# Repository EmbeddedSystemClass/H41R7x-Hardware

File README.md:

# H41R7x-Hardware
Hexabitz STM32F7/H7 LQFP100 Module Hardware Design

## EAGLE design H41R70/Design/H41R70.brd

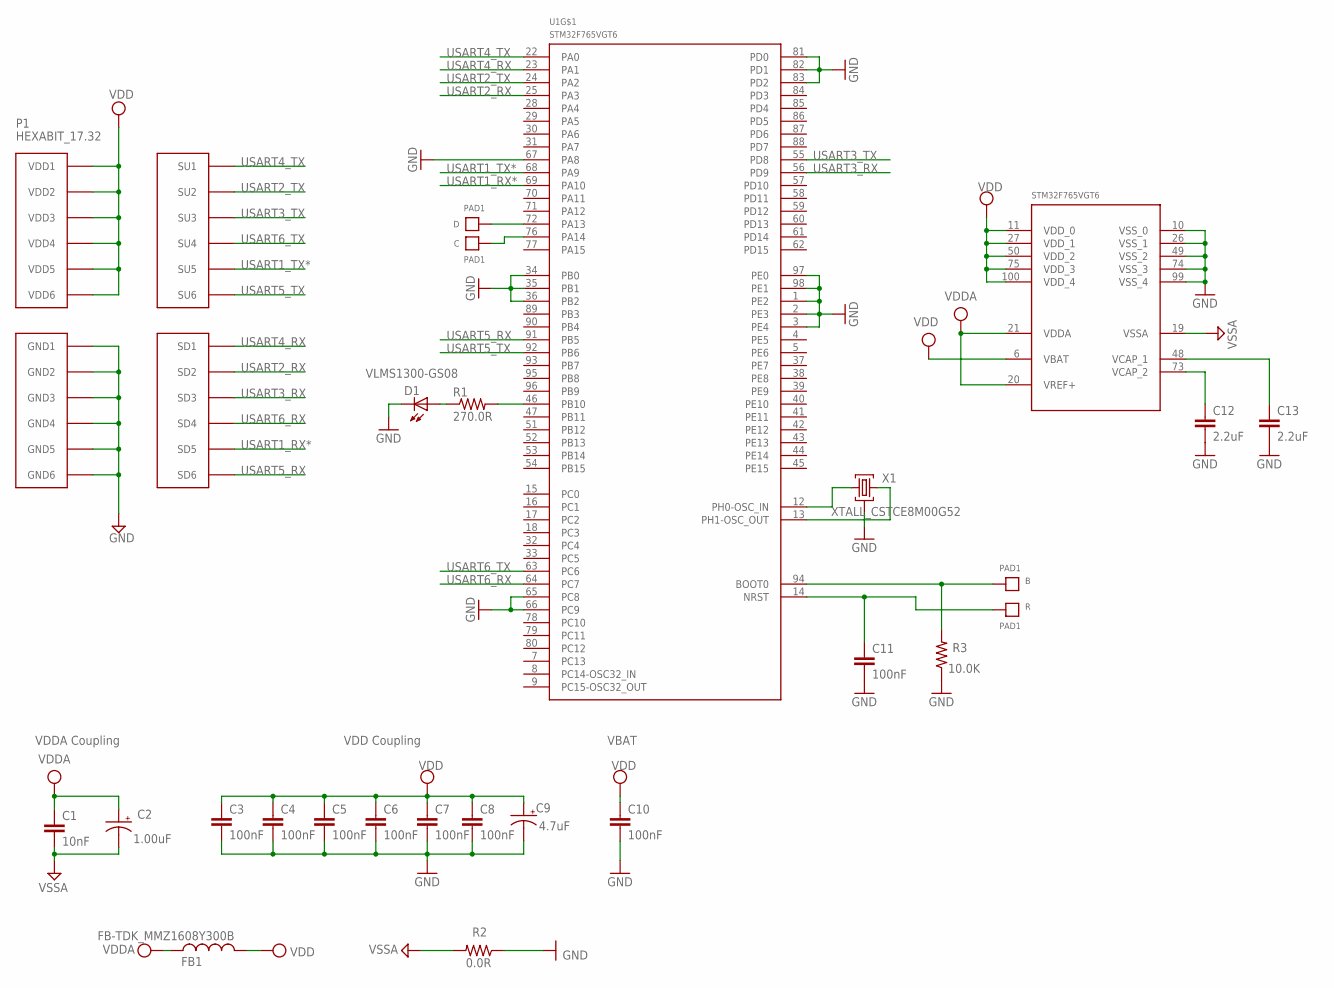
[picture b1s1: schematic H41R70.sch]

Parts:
B: PAD1
C: PAD1
C1: 10nF; C-0603; TOLERANCE 10%; VOLTAGE_RATING 50V; MPN C0603C103K5RACTU
C2: 1.00uF; C-0805-POL; TOLERANCE 10%; VOLTAGE_RATING 16V; MPN CC0805KKX7R7BB105
C3, C4, C5, C6, C8, C11: 100nF; C-0603; TOLERANCE 10%; VOLTAGE_RATING 10V; MPN C0603C104K8RACTU
C7: 100nF; C-0603; TOLERANCE 10%; VOLTAGE_RATING 10; MPN C0603C104K8RACTU
C9: 4.7uF; C-0805-POL; TOLERANCE 10%; VOLTAGE_RATING 25V; MPN GRM21BC81E475KA12L
C10: 100nF; C-0603; TOLERANCE 10V; VOLTAGE_RATING 10%; MPN C0603C104K8RACTU
C12, C13: 2.2uF; C-0603; TOLERANCE 16V; VOLTAGE_RATING 20%; MPN C1608X5R1C225K080AB
D: PAD1
D1: VLMS1300-GS08; MPN VLMS1300-GS08
FB1: FB-TDK_MMZ1608Y300B; MPN MMZ1608Y300B
P1: HEXABIT_17.32
R: PAD1
R1: 270.0R; R-0603; TOLERANCE 1%; MPN RC0603FR-07270RL
R2: 0.0R; R-0603; MPN RC0603JR-070RL
R3: 10.0K; R-0603; TOLERANCE 5%; MPN RC0603JR-0710KL
U1: STM32F765VGT6; LQFP-100
X1: XTALL_CSTCE8M00G52

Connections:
B1: B.P$1, B.P$2, R3.2, U1.94 (BOOT0)
GND: C3.2, C4.2, C5.2, C6.2, C7.2, C8.2, C9.2 (-), C10.2, C11.2, C12.2, C13.2, D1.C, P1.PAD_PD7 (GND1), P1.PAD_PD8 (GND2), P1.PAD_PD9 (GND3), P1.PAD_PD10 (GND4), P1.PAD_PD11 (GND5), P1.PAD_PD12 (GND6), R2.1, R3.1, U1.1 (PE2), U1.2 (PE3), U1.3 (PE4), U1.10 (VSS_0), U1.26 (VSS_1), U1.34 (PB0), U1.35 (PB1), U1.36 (PB2), U1.49 (VSS_2), U1.65 (PC8), U1.66 (PC9), U1.67 (PA8), U1.74 (VSS_3), U1.81 (PD0), U1.82 (PD1), U1.83 (PD2), U1.97 (PE0), U1.98 (PE1), U1.99 (VSS_4), X1.P$2 (2)
unnamed: D.P$1, D.P$2, U1.72 (PA13)
unnamed: C.P$1, C.P$2, U1.76 (PA14)
unnamed: U1.12 (PH0-OSC_IN), X1.P$1 (1)
unnamed: U1.13 (PH1-OSC_OUT), X1.P$3 (3)
unnamed: C12.1, U1.73 (VCAP_2)
unnamed: R1.2, U1.46 (PB10)
unnamed: D1.A, R1.1
unnamed: C13.1, U1.48 (VCAP_1)
R1: C11.1, R.P$1, R.P$2, U1.14 (NRST)
USART1_RX*: P1.PAD_PD5 (SD5), U1.69 (PA10)
USART1_TX*: P1.PAD_PU5 (SU5), U1.68 (PA9)
USART2_RX: P1.PAD_PD2 (SD2), U1.25 (PA3)
USART2_TX: P1.PAD_PU2 (SU2), U1.24 (PA2)
USART3_RX: P1.PAD_PD3 (SD3), U1.56 (PD9)
USART3_TX: P1.PAD_PU3 (SU3), U1.55 (PD8)
USART4_RX: P1.PAD_PD1 (SD1), U1.23 (PA1)
USART4_TX: P1.PAD_PU1 (SU1), U1.22 (PA0)
USART5_RX: P1.PAD_PD6 (SD6), U1.91 (PB5)
USART5_TX: P1.PAD_PU6 (SU6), U1.92 (PB6)
USART6_RX: P1.PAD_PD4 (SD4), U1.64 (PC7)
USART6_TX: P1.PAD_PU4 (SU4), U1.63 (PC6)
VDD: C3.1, C4.1, C5.1, C6.1, C7.1, C8.1, C9.1 (+), C10.1, FB1.2, P1.PAD_PU7 (VDD1), P1.PAD_PU8 (VDD2), P1.PAD_PU9 (VDD3), P1.PAD_PU10 (VDD4), P1.PAD_PU11 (VDD5), P1.PAD_PU12 (VDD6), U1.6 (VBAT), U1.11 (VDD_0), U1.27 (VDD_1), U1.50 (VDD_2), U1.75 (VDD_3), U1.100 (VDD_4)
VDDA: C1.1, C2.1 (+), FB1.1, U1.20 (VREF+), U1.21 (VDDA)
VSSA: C1.2, C2.2 (-), R2.2, U1.19 (VSSA)

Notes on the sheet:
VDDA Coupling
VDD Coupling
VBAT

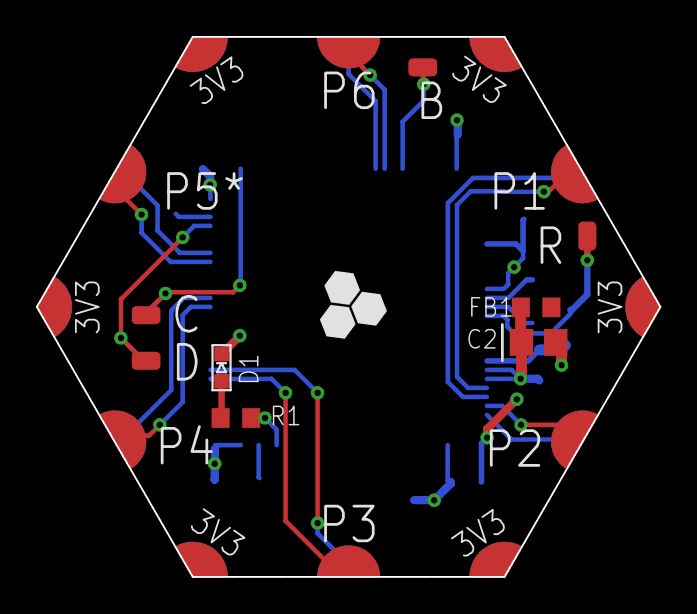
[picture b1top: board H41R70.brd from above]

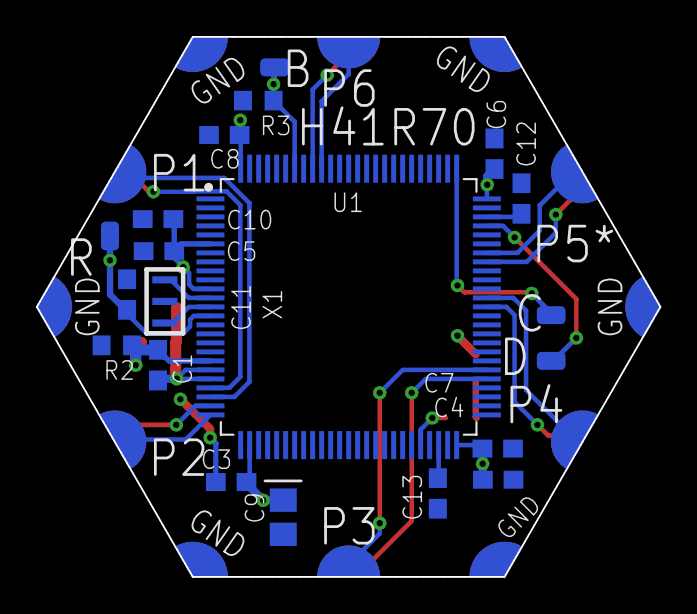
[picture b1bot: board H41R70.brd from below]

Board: 2 copper layers, 34.6 x 30.0 mm, 25 parts (16 on the bottom side), 26 nets.

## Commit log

2019-05-23 First release rev 0
2019-08-19 Update schematics PDF
